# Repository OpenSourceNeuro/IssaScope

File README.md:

<h1 align="center"> Issa Scope v0.2</h1>
<h3 align="center">  An ethoscope for optogenetics behavioural essays</h3></p>
<h6 align="right">developed by M.J.Y. Zimmermann</h6>

<br></br>

This project is licensed under the <a href="https://www.gnu.org/licenses/gpl-3.0.html">GNU General Public License v3.0</a>

The hardware is licensed under the <a href="https://cern-ohl.web.cern.ch">CERN OHL v1.2</a>

<br></br>

***

<br></br>

- [Introduction](#Introduction)
- [EthoScope](#Ethoscope)
- [PCB](#PCB)
- [ESP32/Arduino microcontroller](#Microcontroller)
  - [Driver Installation](#Driver_Installation)
  - [Arduino Environment](#Arduino_IDE)
  - [Compiling and uploading code](#Compiling_the_code)
- [GUI](#GUI)
  - [PyQt Script](#PyQt)
  - [Scope Software](#Software)

- [To-Do-List](#To-Do-List)

<br></br>

***

<br></br>

## Introduction

<br></br>

## Ethoscope
<p align="justify">
The Ethoscope consists of 15mm extruded aluminium bars purchased from <a href="https://www.makerbeam.com/makerbeamxl/">MakerBeam</a> (XL profile), and 3D printed parts.
</p>

<br></br>

## PCB
<br>
<div align= "justify">

<p>
Dedicated PCBs for all electronics components contained in the scope base and platform stimulating LEDs can be found <a href="https://github.com/OpenSourceNeuro/IssaScope/tree/main/PCB"><strong>here</strong></a> along with detailed instructions to reproduce and adapt them.
</p>

<br></br>
<h3 align="left">Ethoscope Main Board</h3></p>

<p>
The PCB is built around an <a href="https://www.espressif.com/en/products/socs/esp32">ESP32</a>, a microcontroller which exchanges signals with the recording setup, and the <a href="https://www.ti.com/lit/ds/symlink/tlc5947.pdf">TLC5947 LED driver</a>, which allows linear intensity control over all stimulating lights. The microcontroller runs on C++ however, users do not need to interfere with the source code as we provide an intuitive and interactive <a href="">Graphical User Interface</a> (GUI), from which all functions and variables can be manipulated.
</p>

<h5 align="center"> <em>Left: </em>PCB schematics for the IssaScope v0.2, <em>Middle: PCB layout for manufacturing</em>, <em>Right: </em>Rendering of the board populated with electronics components</h5>

<br>

<p>
The board provides connections via Molex JST plugs for 4 * four LED channels meant to be used for 4 * four distinct optogenetics light sources.

It also provides ports for base illumination for both white and infra red lights, designed for providing light below the samples.

Remaining ports provide access to unuse GPIO pins on the microcontroller for further upgrade (I/O signals, sensors, motors, etc.)

The board takes a 24V input, a tension above this value will result in damaging the board components.
</p>

<br></br>

<p>
This repository contains detailed <a href="https://github.com/OpenSourceNeuro/OpenSpritzer-V2/blob/main/Installation_Manual.md">assembly instructions and an operation manual</a> for the Scope electronics assembly. The <a href="https://github.com/OpenSourceNeuro/OpenSpritzer-V2/blob/main/BOM.csv">bill of material</a> details all components required.
</p>

<p>
To simplify the wiring assembly, a customed circuit board has been designed. PCB prototype companies (i.e. <a href="jlcpcb.com"> JLCPCB</a>) will only require the <a href="https://github.com/OpenSourceNeuro/IssaScope/tree/main/PCB/IssaScope_gerbers  "> gerber.zip</a> folder to be sent to them for production.
</p>

</div>
<br></br>

## Microcontroller

#### Driver_Installation
<br>
<div align= "justify">

<p>
IssaScope v0.2 firmware runs on an Espressif ESP32 board and requires the USB to UART bridge <a href="https://www.silabs.com/developers/usb-to-uart-bridge-vcp-drivers"> CP210x driver</a>,  which can be downloaded<a href="https://www.silabs.com/developers/usb-to-uart-bridge-vcp-drivers?tab=downloads"> <strong>here</strong></a>.
</p>

<p>
Once the driver has been installed, users can upload and modify the <a href="https://https://github.com/OpenSourceNeuro/IssaScope/tree/main/Arduino/IssaScope.com/OpenSourceNeuro/OpenSpritzer-V2/tree/main/Arduino/OpenSpritzer_V2">microcontroller code</a> through the <a href="https://www.arduino.cc/en/software">Arduino IDE</a> (Integrated Development Environment).
</p>

</div>
<br></br>

##### Arduino_IDE
<br>
<div align="justify">

<p>
The ESP32 microcontroller runs a C++ code which can be accessed via the Arduino IDE, which can be downloaded <a href="https://www.arduino.cc/en/software"><strong>here</strong></a>.
</p>

<br></br>

<p>

Once the IDE is installed, users needs to install the ESP32 board library:

In the Arduino IDE, go to <strong> File > Preferences </strong>

Enter the following link into the <strong>Additional Board Manager URLs</strong> field:

https://raw.githubusercontent.com/espressif/arduino-esp32/gh-pages/package_esp32_index.json
</p>

<br></br>

<p>

Then click on the <strong>OK</strong> button.
</p>

<br></br>

<p>
Next, open the Boards Manager. Go to <strong> Tools > Board > Board Manager...</strong>

Search for ESP32 and press install button for the <strong>ESP32 by Espressif Systems</strong>.
</p>

<br></br>

<p>

Then click on the <strong>Install</strong> button.
</p>

<br></br>

<p>
Finally and in a smiilar manner the library <strong>Adafruit_TLC5947</strong> needs to be installed.
</p>

</div>
<br></br>

##### Compiling_the_code
<br>
<div align= "justify">

<p>
Within the Arduino IDE, user needs to select the FQBN (Fully Qualified Board Name) on which the code will be compiled for.

Here the ESP32 Dev Module needs to be selected.

Go to <strong>Tools > Board > esp32 > ESP32 Dev Module </strong>

The board name should be displayed  as shown.
</p>

</div>
<br></br>

## GUI
<div align="justify">

<p>
A Graphical User Interface (GUI) dedicated to this project was designed using the python PyQt6/PySide6 libraries. The entire script can be found <a href="https://github.com/OpenSourceNeuro/IssaScope/tree/main/GUI/PyQt"><strong>here</strong></a>.
</p>

</div>
<br></br>

#### PyQt
<br>
<div align="justify">

githubusercontent

<br></br>

#### Software
<br>
<div align="justify">

<p>
The python script for the GUI can be run directly from a python environment, or run from a <strong>.exe</strong> file which can be found <a href=""><strong>here</strong></a>
</p>

<p>
On the main screen, Users can fi
</p>

</div>
<br></br>

## To-Do-List
<br>
<div align="justify">

- Find suitable material for close up hanging LEDs
- Make an equivalent to the GUI using Bonsai

</div>
<br></br>

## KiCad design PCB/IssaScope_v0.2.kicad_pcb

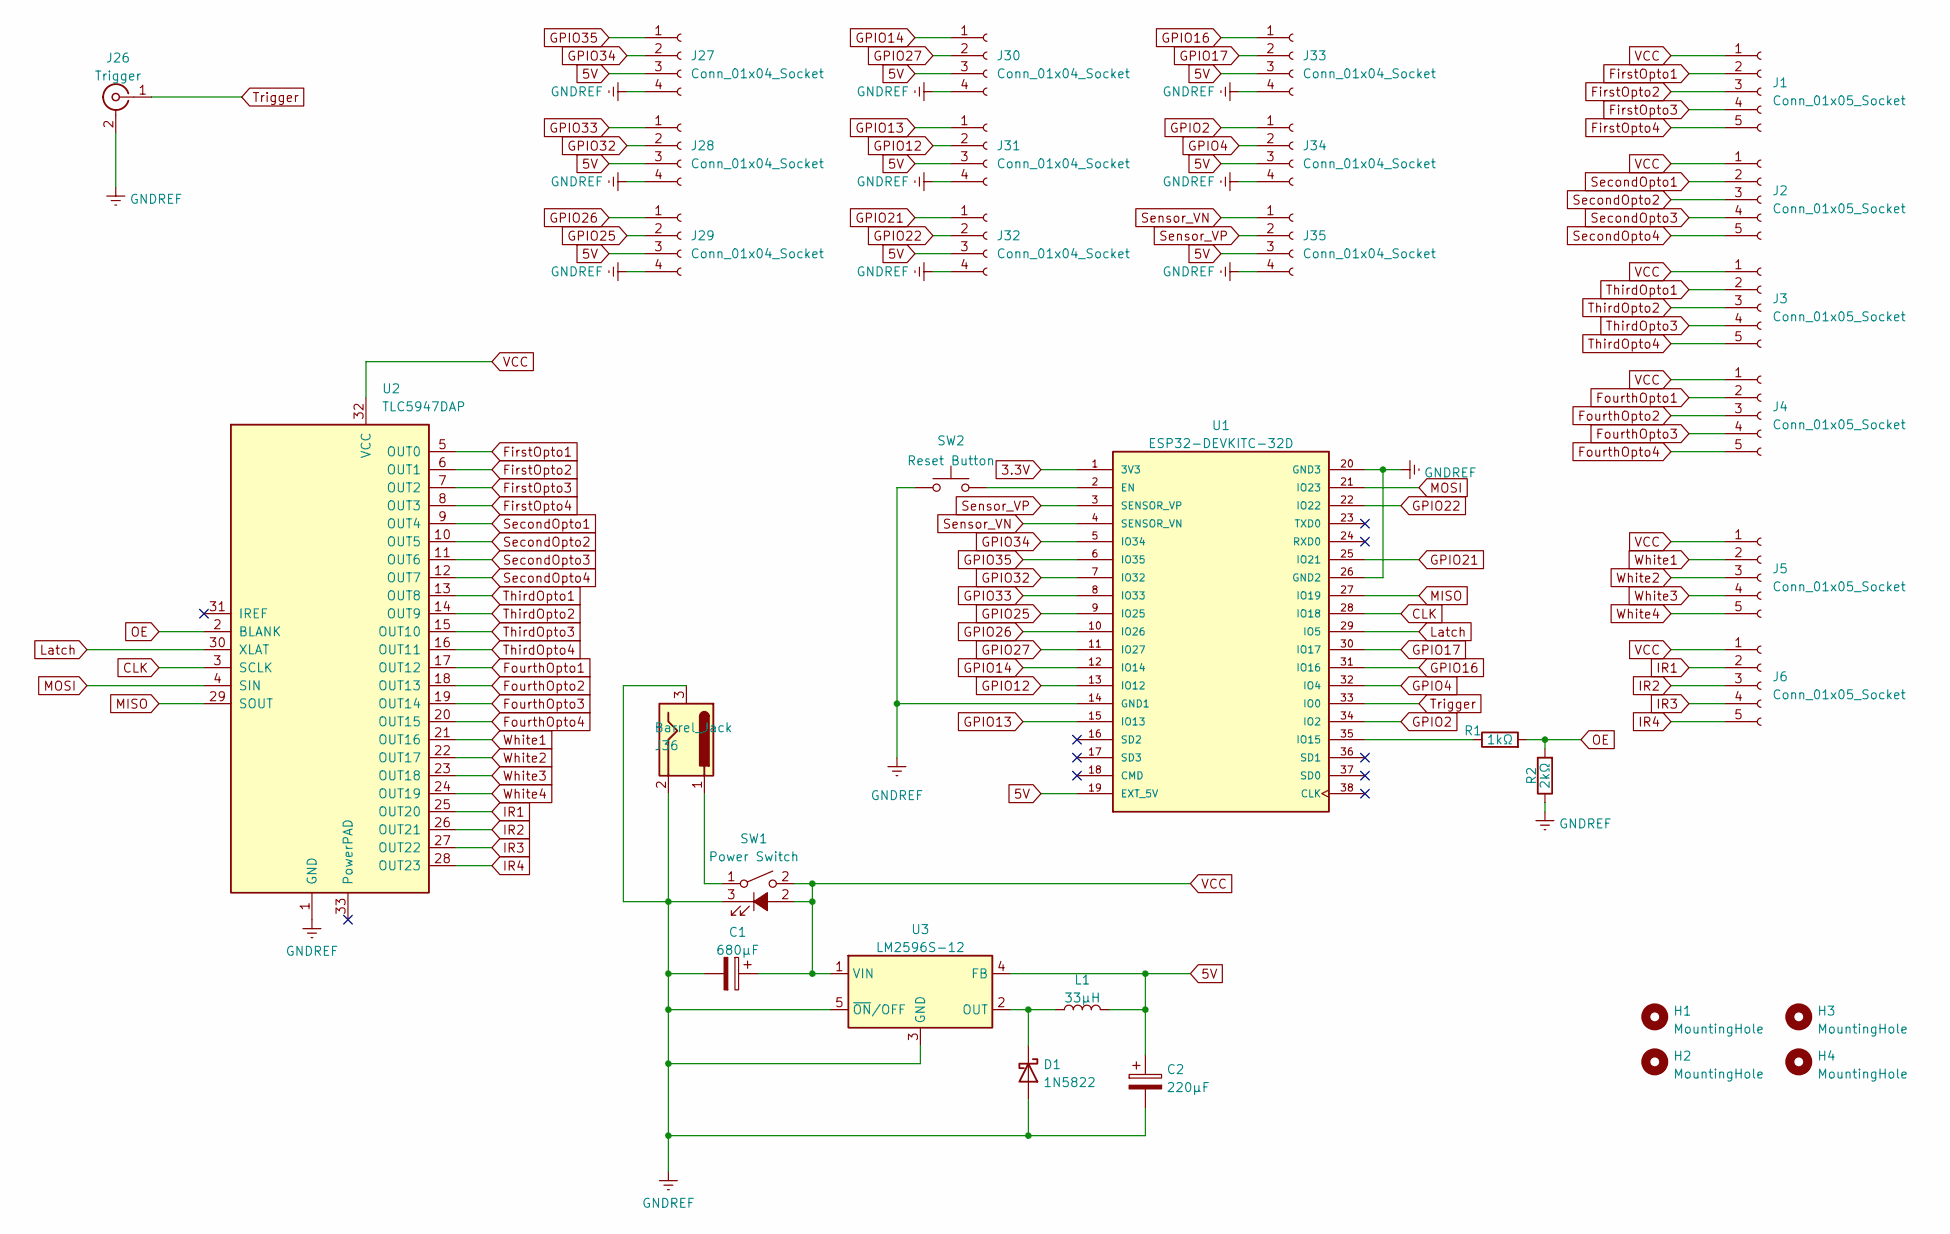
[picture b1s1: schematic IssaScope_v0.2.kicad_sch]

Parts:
C1: 680μF; CP_Radial_D6.3mm_P2.50mm
C2: 220μF; CP_Radial_D6.3mm_P2.50mm
D1: 1N5822; D_DO-201AD_P15.24mm_Horizontal
H1, H2, H3, H4: MountingHole; MountingHole_3mm
J1, J2, J3, J4, J5, J6: Conn_01x05_Socket; JST_XH_S5B-XH-A_1x05_P2.50mm_Horizontal
J26: Trigger; BNC_Socket_TYCO-AMP_LargePads
J27, J28, J29, J30, J31, J32, J33, J34, J35: Conn_01x04_Socket; JST_XH_S4B-XH-A_1x04_P2.50mm_Horizontal
J36: Barrel_Jack; BarrelJack_Horizontal
L1: 33μH; L_Radial_D6.0mm_P4.00mm
R1: 1kΩ; R_Axial_DIN0309_L9.0mm_D3.2mm_P15.24mm_Horizontal
R2: 2kΩ; R_Axial_DIN0309_L9.0mm_D3.2mm_P15.24mm_Horizontal
SW1: Power Switch; JST_XH_B3B-XH-A_1x03_P2.50mm_Vertical
SW2: Reset Button; SW_Tactile_SPST_Angled_PTS645Vx39-2LFS
U1: ESP32-DEVKITC-32D; MODULE_ESP32-DEVKITC-32D; PARTREV 4
U2: TLC5947DAP; Maxi_TLC5947
U3: LM2596S-12; TO-220-5_P3.4x3.7mm_StaggerOdd_Lead3.8mm_Vertical

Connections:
3.3V: U1.1 (3V3)
5V: C2.1, J27.3, J28.3, J29.3, J30.3, J31.3, J32.3, J33.3, J34.3, J35.3, L1.2, U1.19 (EXT_5V), U3.4 (FB)
CLK: U1.28 (IO18), U2.3 (SCLK)
FirstOpto1: J1.2, U2.5 (OUT0)
FirstOpto2: J1.3, U2.6 (OUT1)
FirstOpto3: J1.4, U2.7 (OUT2)
FirstOpto4: J1.5, U2.8 (OUT3)
FourthOpto1: J4.2, U2.17 (OUT12)
FourthOpto2: J4.3, U2.18 (OUT13)
FourthOpto3: J4.4, U2.19 (OUT14)
FourthOpto4: J4.5, U2.20 (OUT15)
GNDREF: C1.2, C2.2, D1.2 (A), J26.2 (Ext), J27.4, J28.4, J29.4, J30.4, J31.4, J32.4, J33.4, J34.4, J35.4, J36.2, J36.3, R2.1, SW1.3 (K), SW2.1, U1.14 (GND1), U1.20 (GND3), U1.26 (GND2), U2.1 (GND), U3.3 (GND), U3.5 (~ON/OFF)
GPIO2: J34.1, U1.34 (IO2)
GPIO4: J34.2, U1.32 (IO4)
GPIO12: J31.2, U1.13 (IO12)
GPIO13: J31.1, U1.15 (IO13)
GPIO14: J30.1, U1.12 (IO14)
GPIO16: J33.1, U1.31 (IO16)
GPIO17: J33.2, U1.30 (IO17)
GPIO21: J32.1, U1.25 (IO21)
GPIO22: J32.2, U1.22 (IO22)
GPIO25: J29.2, U1.9 (IO25)
GPIO26: J29.1, U1.10 (IO26)
GPIO27: J30.2, U1.11 (IO27)
GPIO32: J28.2, U1.7 (IO32)
GPIO33: J28.1, U1.8 (IO33)
GPIO34: J27.2, U1.5 (IO34)
GPIO35: J27.1, U1.6 (IO35)
IR1: J6.2, U2.25 (OUT20)
IR2: J6.3, U2.26 (OUT21)
IR3: J6.4, U2.27 (OUT22)
IR4: J6.5, U2.28 (OUT23)
Latch: U1.29 (IO5), U2.30 (XLAT)
MISO: U1.27 (IO19), U2.29 (SOUT)
MOSI: U1.21 (IO23), U2.4 (SIN)
unnamed: D1.1 (K), L1.1, U3.2 (OUT)
unnamed: J36.1, SW1.1
unnamed: SW2.2, U1.2 (EN)
unnamed: R1.1, U1.35 (IO15)
OE: R1.2, R2.2, U2.2 (BLANK)
SecondOpto1: J2.2, U2.9 (OUT4)
SecondOpto2: J2.3, U2.10 (OUT5)
SecondOpto3: J2.4, U2.11 (OUT6)
SecondOpto4: J2.5, U2.12 (OUT7)
Sensor_VN: J35.1, U1.4 (SENSOR_VN)
Sensor_VP: J35.2, U1.3 (SENSOR_VP)
ThirdOpto1: J3.2, U2.13 (OUT8)
ThirdOpto2: J3.3, U2.14 (OUT9)
ThirdOpto3: J3.4, U2.15 (OUT10)
ThirdOpto4: J3.5, U2.16 (OUT11)
Trigger: J26.1 (In), U1.33 (IO0)
VCC: C1.1, J1.1, J2.1, J3.1, J4.1, J5.1, J6.1, SW1.2, U2.32 (VCC), U3.1 (VIN)
White1: J5.2, U2.21 (OUT16)
White2: J5.3, U2.22 (OUT17)
White3: J5.4, U2.23 (OUT18)
White4: J5.5, U2.24 (OUT19)

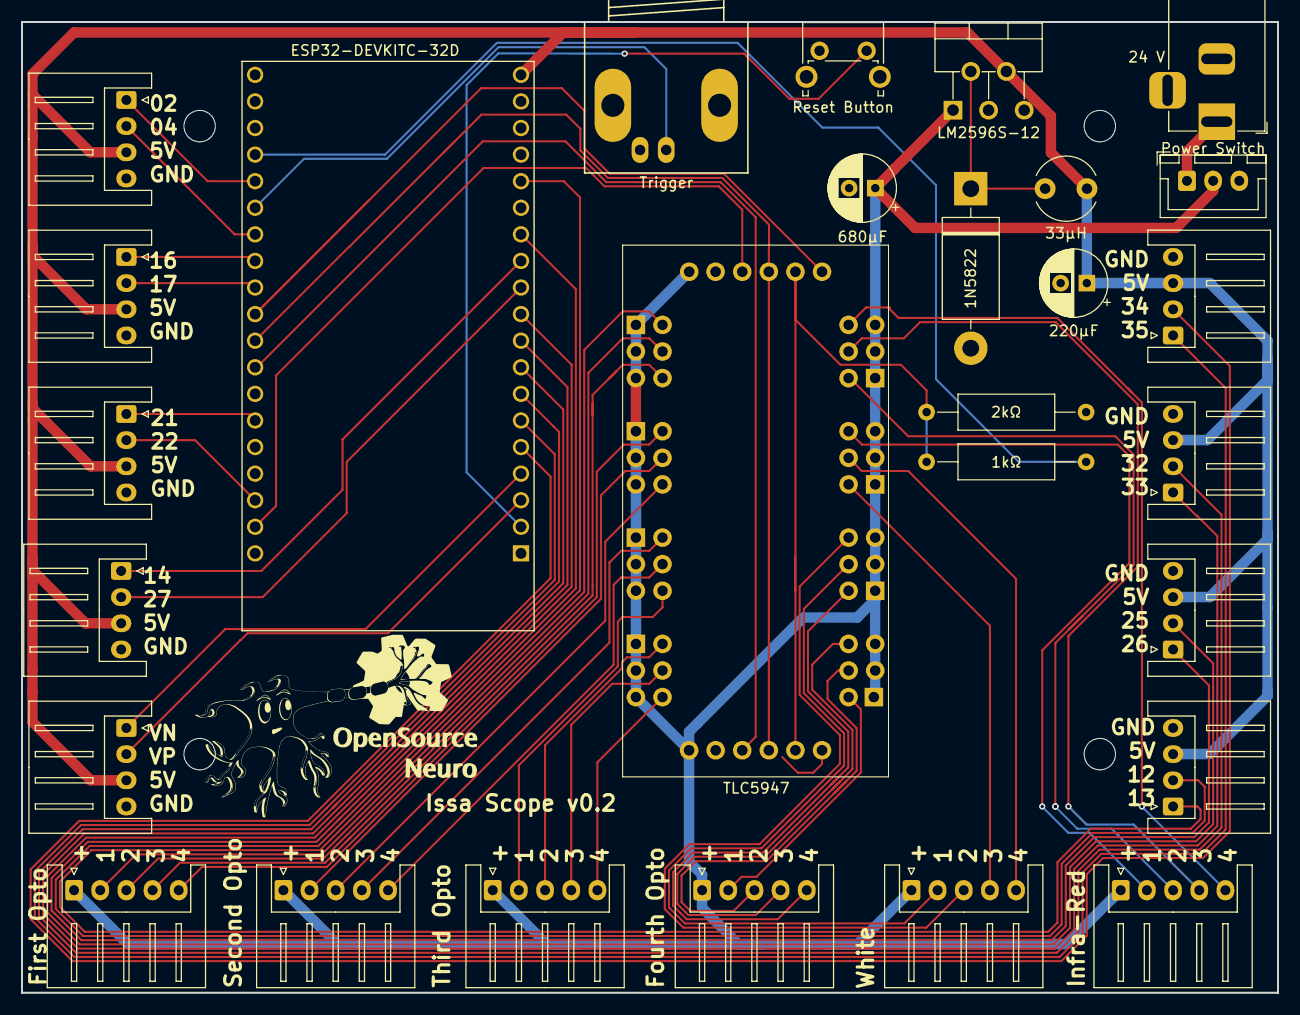
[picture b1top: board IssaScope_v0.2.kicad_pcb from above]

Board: 2 copper layers, 120.0 x 92.8 mm, 32 parts (0 on the bottom side), 55 nets.

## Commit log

2024-01-27 Create 3D folder
2024-01-27 create Arduino folder
2024-01-27 create GUI Folder
2024-02-29 Update 3D
2024-02-29 update Arduino
2024-02-29 update GUI
2024-05-20 upload 3D files
2024-05-21 update PCB
2024-05-21 update Images
2024-05-23 update GUI files
